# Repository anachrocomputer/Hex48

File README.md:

# Hex48 #

PCB design for a hexagonal prototyping board capable of holding DIL chips with
up to 48 pins.

## The Problem ##

Everybody has prototyping PCBs in rectangular form, but what other shapes tesselate well?
How about hexagons, would they work?
And why stop at 40-pin DIL packages when chips like the 68008 come in 48-pin DIL?

## The Solution ##

This PCB design mounts the DIL part on a hexagonal board that can be easily tesselated.
It has mounting holes for M3 PCB standoffs, or it can be fitted with non-slip feet.
In extreme cases, a heavy base can be made out of an insulator such as slate.

## KiCad ##

This design has been created using the Open Source CAD package KiCad, V8.0.

To install it on Ubuntu Linux:

`sudo add-apt-repository ppa:kicad/kicad-8.0-releases`

`sudo apt update`

`sudo apt install kicad`

I'm using Ubuntu 22.04 LTS which would give me the very outdated KiCad V6.0 by default.
As I write this, the latest KiCad is V8.0.5,
which is a big upgrade from the V6.0 which I started with.

## PCB Photo ##
Photo of the PCB, as manufactured.

PCB with sockets and headers soldered on, mounted on a base made out of slate.

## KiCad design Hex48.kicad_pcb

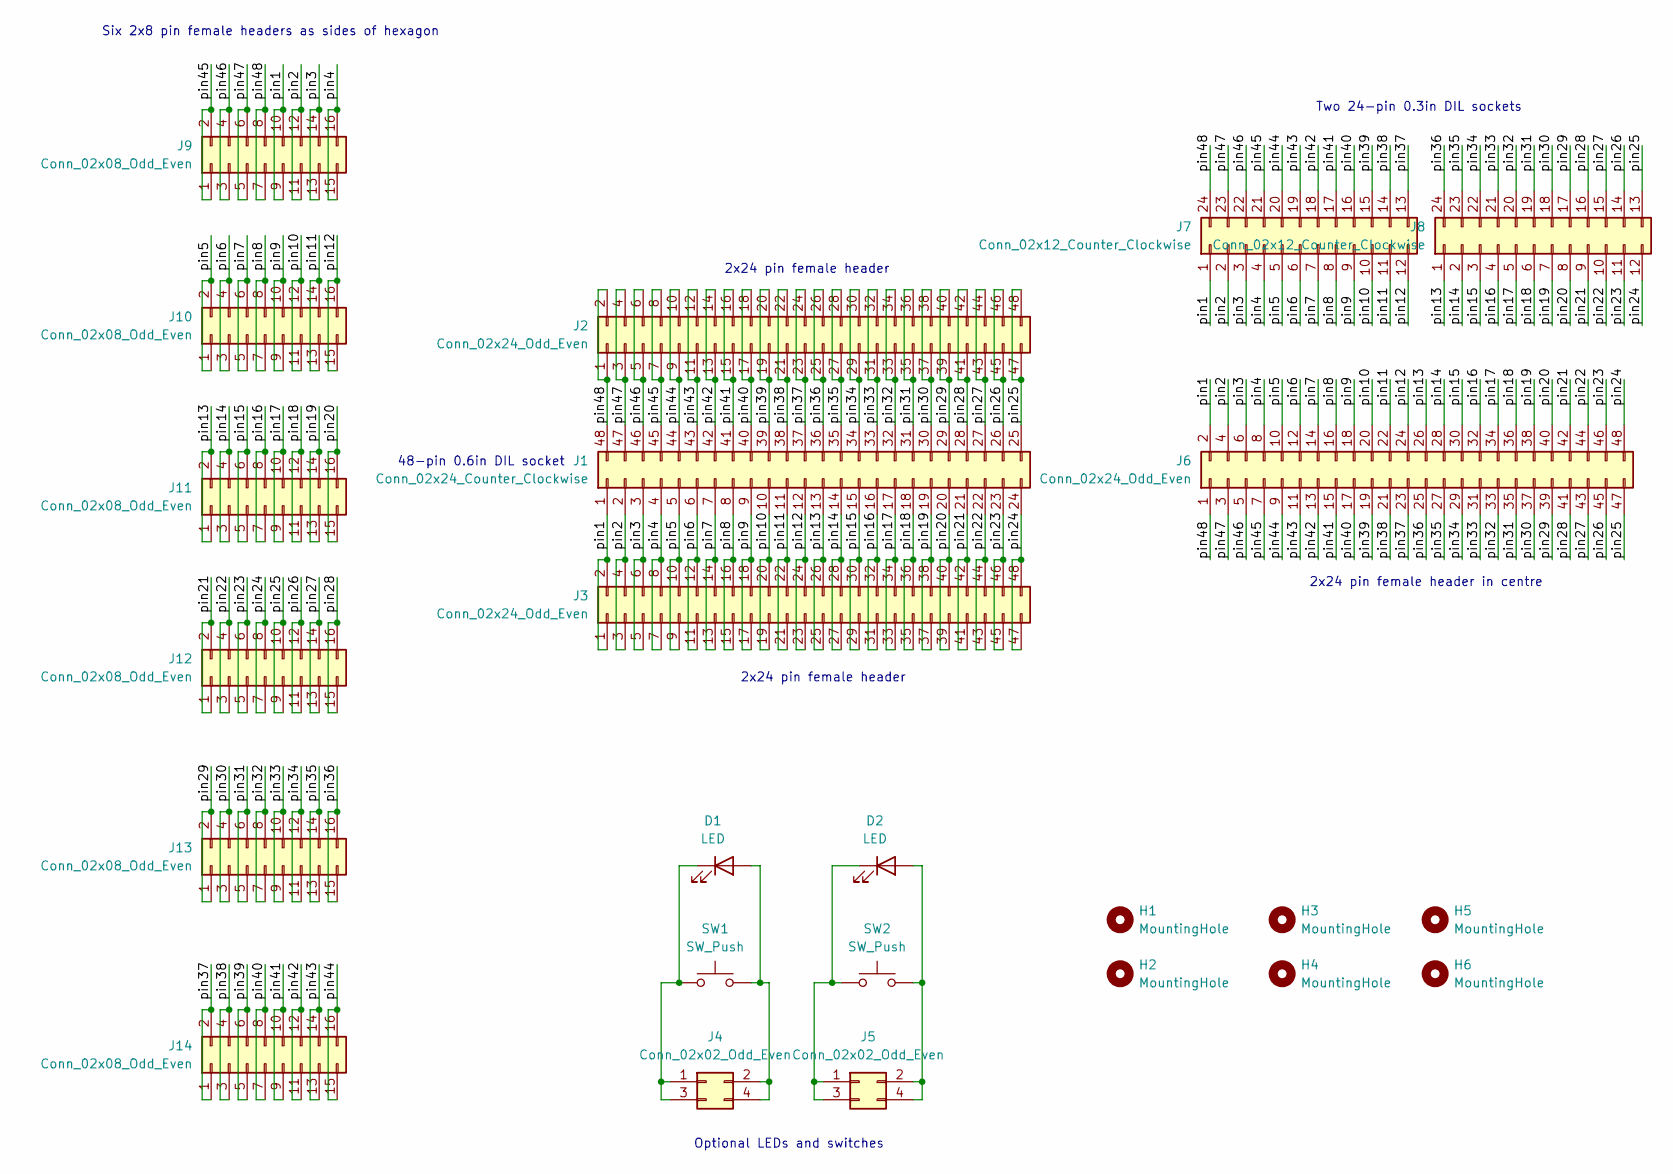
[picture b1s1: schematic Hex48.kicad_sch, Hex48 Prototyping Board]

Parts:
D1, D2: LED; LED_D10.0mm
H1, H2, H3, H4, H5, H6: MountingHole; MountingHole_3.2mm_M3_Pad
J1: Conn_02x24_Counter_Clockwise; DIP-48_W15.24mm_Socket_LongPads
J2, J3, J6: Conn_02x24_Odd_Even; PinSocket_2x24_P2.54mm_Vertical
J4, J5: Conn_02x02_Odd_Even; PinSocket_2x02_P2.54mm_Vertical
J7, J8: Conn_02x12_Counter_Clockwise; DIP-24_W7.62mm_Socket_LongPads
J9, J10, J11, J12, J13, J14: Conn_02x08_Odd_Even; PinSocket_2x08_P2.54mm_Vertical
SW1, SW2: SW_Push; SW_PUSH_6mm

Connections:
/pin1: J1.1, J3.1, J3.2, J6.2, J7.1, J9.9, J9.10
/pin2: J1.2, J3.3, J3.4, J6.4, J7.2, J9.11, J9.12
/pin3: J1.3, J3.5, J3.6, J6.6, J7.3, J9.13, J9.14
/pin4: J1.4, J3.7, J3.8, J6.8, J7.4, J9.15, J9.16
/pin5: J1.5, J3.9, J3.10, J6.10, J7.5, J10.1, J10.2
/pin6: J1.6, J3.11, J3.12, J6.12, J7.6, J10.3, J10.4
/pin7: J1.7, J3.13, J3.14, J6.14, J7.7, J10.5, J10.6
/pin8: J1.8, J3.15, J3.16, J6.16, J7.8, J10.7, J10.8
/pin9: J1.9, J3.17, J3.18, J6.18, J7.9, J10.9, J10.10
/pin10: J1.10, J3.19, J3.20, J6.20, J7.10, J10.11, J10.12
/pin11: J1.11, J3.21, J3.22, J6.22, J7.11, J10.13, J10.14
/pin12: J1.12, J3.23, J3.24, J6.24, J7.12, J10.15, J10.16
/pin13: J1.13, J3.25, J3.26, J6.26, J8.1, J11.1, J11.2
/pin14: J1.14, J3.27, J3.28, J6.28, J8.2, J11.3, J11.4
/pin15: J1.15, J3.29, J3.30, J6.30, J8.3, J11.5, J11.6
/pin16: J1.16, J3.31, J3.32, J6.32, J8.4, J11.7, J11.8
/pin17: J1.17, J3.33, J3.34, J6.34, J8.5, J11.9, J11.10
/pin18: J1.18, J3.35, J3.36, J6.36, J8.6, J11.11, J11.12
/pin19: J1.19, J3.37, J3.38, J6.38, J8.7, J11.13, J11.14
/pin20: J1.20, J3.39, J3.40, J6.40, J8.8, J11.15, J11.16
/pin21: J1.21, J3.41, J3.42, J6.42, J8.9, J12.1, J12.2
/pin22: J1.22, J3.43, J3.44, J6.44, J8.10, J12.3, J12.4
/pin23: J1.23, J3.45, J3.46, J6.46, J8.11, J12.5, J12.6
/pin24: J1.24, J3.47, J3.48, J6.48, J8.12, J12.7, J12.8
/pin25: J1.25, J2.47, J2.48, J6.47, J8.13, J12.9, J12.10
/pin26: J1.26, J2.45, J2.46, J6.45, J8.14, J12.11, J12.12
/pin27: J1.27, J2.43, J2.44, J6.43, J8.15, J12.13, J12.14
/pin28: J1.28, J2.41, J2.42, J6.41, J8.16, J12.15, J12.16
/pin29: J1.29, J2.39, J2.40, J6.39, J8.17, J13.1, J13.2
/pin30: J1.30, J2.37, J2.38, J6.37, J8.18, J13.3, J13.4
/pin31: J1.31, J2.35, J2.36, J6.35, J8.19, J13.5, J13.6
/pin32: J1.32, J2.33, J2.34, J6.33, J8.20, J13.7, J13.8
/pin33: J1.33, J2.31, J2.32, J6.31, J8.21, J13.9, J13.10
/pin34: J1.34, J2.29, J2.30, J6.29, J8.22, J13.11, J13.12
/pin35: J1.35, J2.27, J2.28, J6.27, J8.23, J13.13, J13.14
/pin36: J1.36, J2.25, J2.26, J6.25, J8.24, J13.15, J13.16
/pin37: J1.37, J2.23, J2.24, J6.23, J7.13, J14.1, J14.2
/pin38: J1.38, J2.21, J2.22, J6.21, J7.14, J14.3, J14.4
/pin39: J1.39, J2.19, J2.20, J6.19, J7.15, J14.5, J14.6
/pin40: J1.40, J2.17, J2.18, J6.17, J7.16, J14.7, J14.8
/pin41: J1.41, J2.15, J2.16, J6.15, J7.17, J14.9, J14.10
/pin42: J1.42, J2.13, J2.14, J6.13, J7.18, J14.11, J14.12
/pin43: J1.43, J2.11, J2.12, J6.11, J7.19, J14.13, J14.14
/pin44: J1.44, J2.9, J2.10, J6.9, J7.20, J14.15, J14.16
/pin45: J1.45, J2.7, J2.8, J6.7, J7.21, J9.1, J9.2
/pin46: J1.46, J2.5, J2.6, J6.5, J7.22, J9.3, J9.4
/pin47: J1.47, J2.3, J2.4, J6.3, J7.23, J9.5, J9.6
/pin48: J1.48, J2.1, J2.2, J6.1, J7.24, J9.7, J9.8
unnamed: D1.2 (A), J4.2, J4.4, SW1.2
unnamed: D1.1 (K), J4.1, J4.3, SW1.1
unnamed: D2.2 (A), J5.2, J5.4, SW2.2
unnamed: D2.1 (K), J5.1, J5.3, SW2.1

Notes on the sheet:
2x24 pin female header
Six 2x8 pin female headers as sides of hexagon
Optional LEDs and switches
Two 24-pin 0.3in DIL sockets
2x24 pin female header in centre
48-pin 0.6in DIL socket

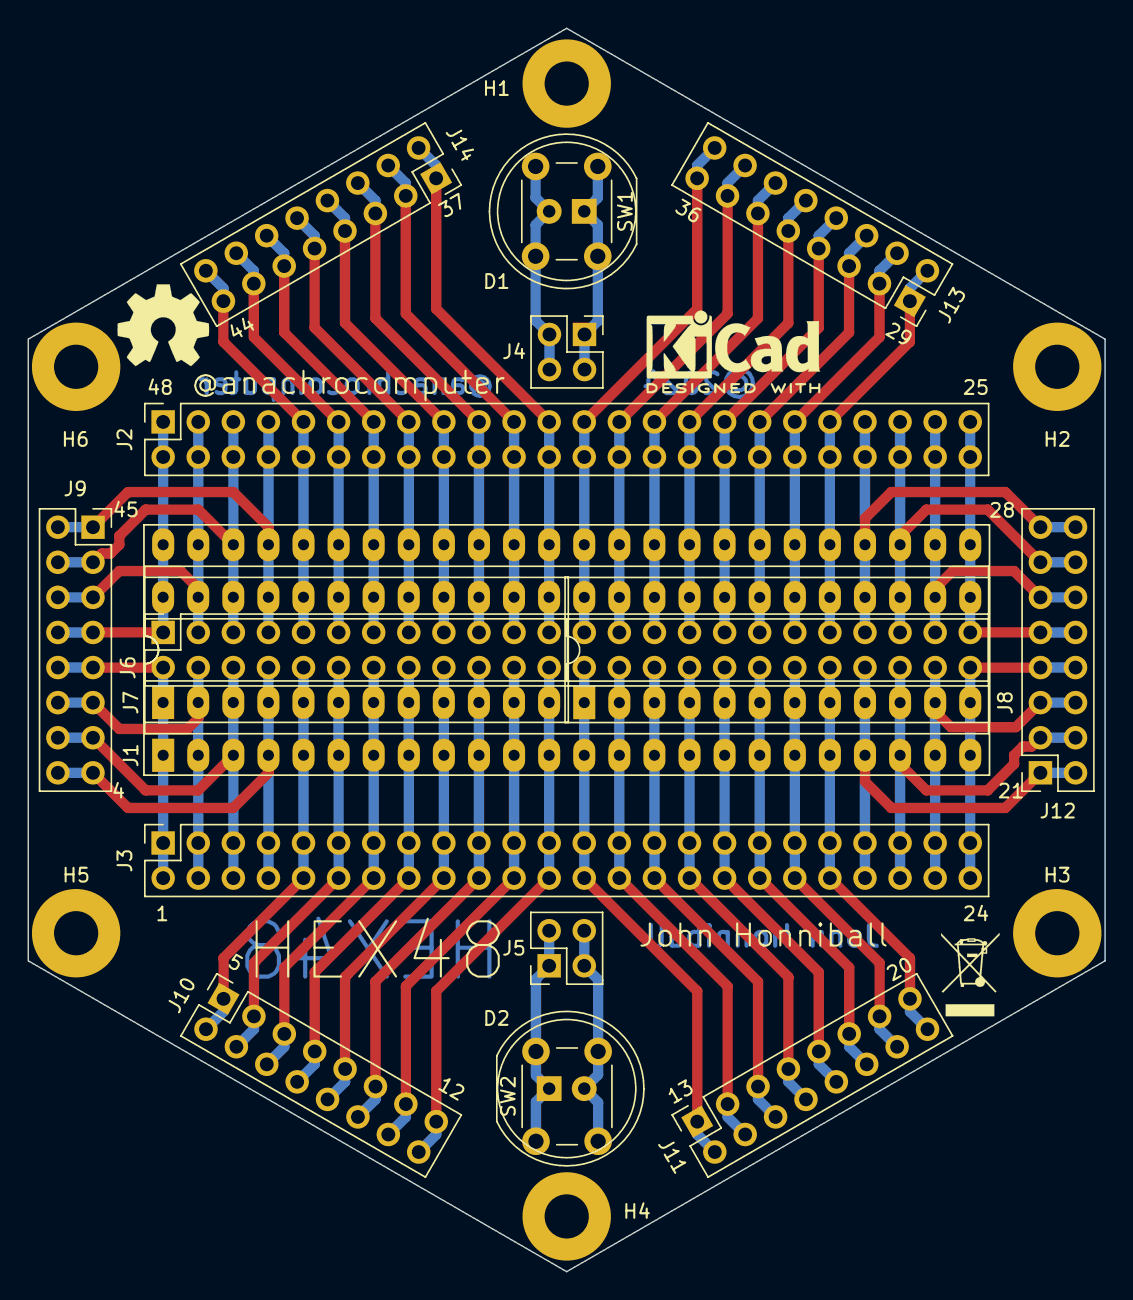
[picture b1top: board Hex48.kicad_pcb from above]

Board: 2 copper layers, 77.9 x 90.0 mm, 24 parts (0 on the bottom side), 52 nets.

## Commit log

2023-08-28 Initial commit.
    Really early version, mostly just to see if the parts fit. No Schematic yet, but does a PCB like this even need a schematic?
2024-09-27 Big upgrade to KiCad V8.0.
    Automatic upgrade seemed to go OK.
2024-10-09 Begin adding schematic.
    Board is much better designed by using a proper schematic instead of just a PCB. But to do that, we need lots of generic connectors, all connected together in a way that only makes sense on the physi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
2024-10-09 Add title block info.
2024-10-10 Finish DIL wiring.
    Place two 24-pin narrow DIL sockets and connect them to the 48-pin wide DIL socket. Name all pin signals.
2024-10-10 Fix heinous typo.
    Also add designer's name and update datestamp.
2024-10-10 Finish schematic, map all footprints,update PCB.
    Rats-nest now complete. Some parts placed on PCB in final locations. Some parts (mounting holes and 2x8 headers) need to be placed exactly on a polar grid at 60-degree intervals.
2024-10-11 Final schematic, V1.0.
    Add some text comments.
2024-10-11 Place footprints on PCB in exact locations.
    PCB edges, mounting holes, connectors, and LEDs/switches in correct places. Footprints locked to avoid mistakes. Initial rear copper tracks added. Dimensions of hexagon and mounting holes added. TODO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
2024-10-12 Route all tracks.
    Try to put tracks on top where they will be visible and self-documenting. Tracks at 45 degrees under 60-degree mounted headers look a bit odd, but they work. All tracks 0.75mm wide. Some spacings a b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
2024-10-13 Move eight tracks just a little bit further from the sockets.
2024-10-13 Add pin numbers to silkscreen.
    Just a few, because the true pin number will change if you fit a 40-pin chip, or two 24-pin chips, or three 16-pin chips. Better to follow the tracks visually.
2024-10-13 Add silkscreen and back copper text.
    KiCad logo, OSHW logo, WEEE logo, name, designers name, date. That Twitter handle is going to look very old very quickly.
2024-10-13 V1.0: ready to go to fab.
    Also add PDFs of schematic and PCB.
2024-11-20 Add photo of finished board.
    Remove dire warning.
2024-11-20 Add photo of populated PCB.
2025-06-11 Add badges.

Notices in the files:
Hex48.kicad_pcb:
©2024
